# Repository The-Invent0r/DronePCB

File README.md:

# DronePCB
Drone PCB design using an Atmega328P microcontroller, MPU6050 IMU, and NRF24L01 radio module

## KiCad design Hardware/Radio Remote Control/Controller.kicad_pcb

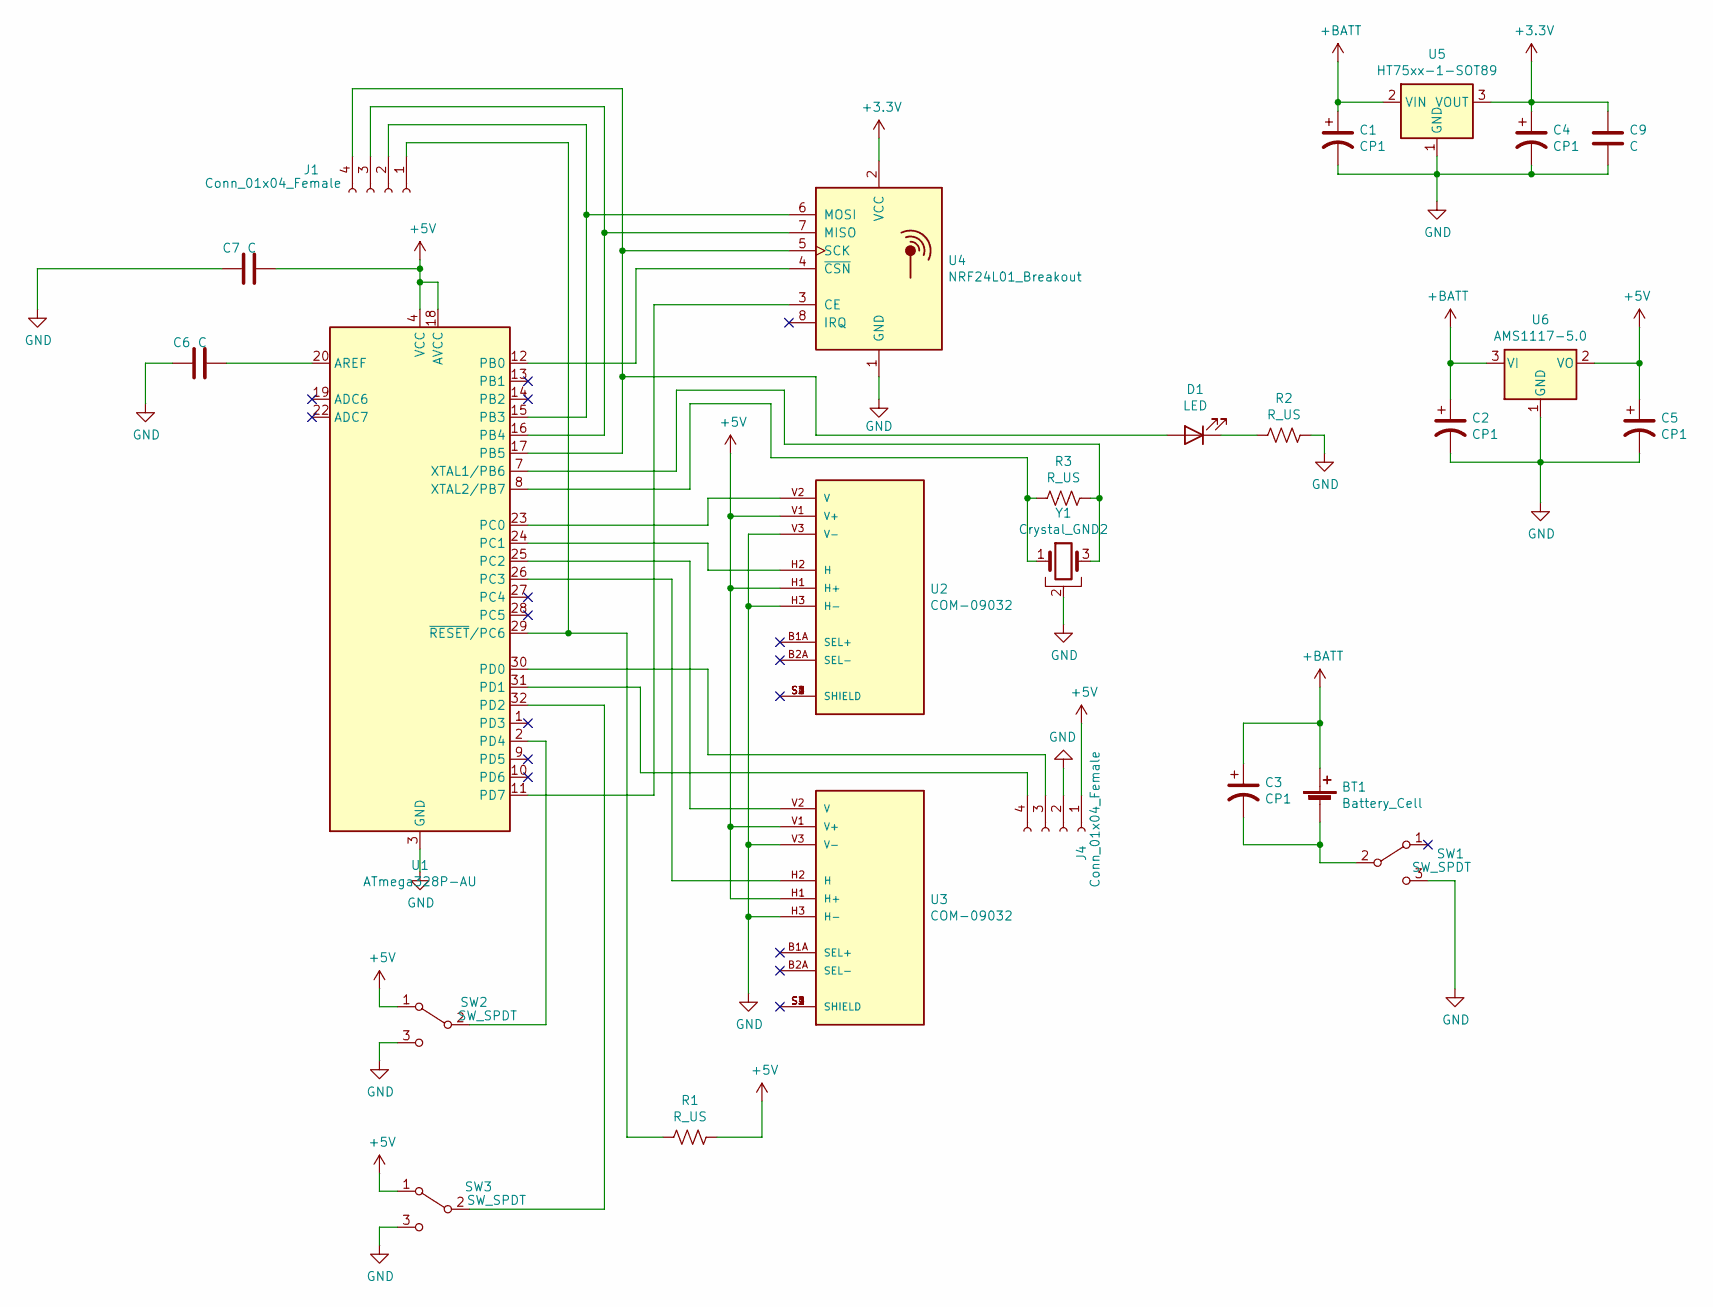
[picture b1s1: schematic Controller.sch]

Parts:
BT1: Battery_Cell; BatteryHolder_Eagle_12BH611-GR
C1, C2, C3, C4, C5: CP1; CP_EIA-3216-10_Kemet-I
C6, C7, C9: C; C_1206_3216Metric_Pad1.33x1.80mm_HandSolder
D1: LED; LED_1206_3216Metric_Pad1.42x1.75mm_HandSolder
J1, J4: Conn_01x04_Female; PinHeader_1x04_P2.54mm_Horizontal
R1, R2, R3: R_US; R_1206_3216Metric_Pad1.30x1.75mm_HandSolder
SW1, SW2, SW3: SW_SPDT; SW_Slide_1P2T_CK_OS102011MS2Q
U1: ATmega328P-AU; TQFP-32_7x7mm_P0.8mm
U2, U3: COM-09032; PARTREV N/A
U4: NRF24L01_Breakout; nRF24L01_Breakout
U5: HT75xx-1-SOT89; SOT-89-3
U6: AMS1117-5.0; SOT-223-3_TabPin2
Y1: Crystal_GND2; Resonator_SMD_muRata_CSTxExxV-3Pin_3.0x1.1mm

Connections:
+3V3: C4.1, C9.1, U4.2 (VCC), U5.3 (VOUT)
+5V: C5.1, C7.2, J4.1, R1.1, SW2.1 (A), SW3.1 (A), U1.4 (VCC), U1.6 (VCC), U1.18 (AVCC), U2.H1 (H+), U2.V1 (V+), U3.H1 (H+), U3.V1 (V+), U6.2 (VO)
+BATT: BT1.1 (+), C1.1, C2.1, C3.1, U5.2 (VIN), U6.3 (VI)
GND: C1.2, C2.2, C4.2, C5.2, C6.1, C7.1, C9.2, J4.2, R2.1, SW1.3 (C), SW2.3 (C), SW3.3 (C), U1.3 (GND), U1.5 (GND), U1.21 (GND), U2.H3 (H-), U2.V3 (V-), U3.H3 (H-), U3.V3 (V-), U4.1 (GND), U5.1 (GND), U6.1 (GND), Y1.2
unnamed: BT1.2 (-), C3.2, SW1.2 (B)
unnamed: C6.2, U1.20 (AREF)
unnamed: D1.1 (K), R2.2
unnamed: D1.2 (A), J1.4, U1.17 (PB5), U4.5 (SCK)
unnamed: J1.1, R1.2, U1.29 (~RESET~/PC6)
unnamed: J1.2, U1.15 (PB3), U4.6 (MOSI)
unnamed: J1.3, U1.16 (PB4), U4.7 (MISO)
unnamed: J4.3, U1.30 (PD0)
unnamed: J4.4, U1.31 (PD1)
unnamed: R3.1, U1.7 (XTAL1/PB6), Y1.3
unnamed: R3.2, U1.8 (XTAL2/PB7), Y1.1
unnamed: SW2.2 (B), U1.2 (PD4)
unnamed: SW3.2 (B), U1.32 (PD2)
unnamed: U1.11 (PD7), U4.3 (CE)
unnamed: U1.12 (PB0), U4.4 (~CSN)
unnamed: U1.23 (PC0), U2.V2 (V)
unnamed: U1.24 (PC1), U2.H2 (H)
unnamed: U1.25 (PC2), U3.V2 (V)
unnamed: U1.26 (PC3), U3.H2 (H)
unnamed: U2.S1 (SHIELD), U2.S2 (SHIELD), U2.S3 (SHIELD), U2.S4 (SHIELD)
unnamed: U3.S1 (SHIELD), U3.S2 (SHIELD), U3.S3 (SHIELD), U3.S4 (SHIELD)

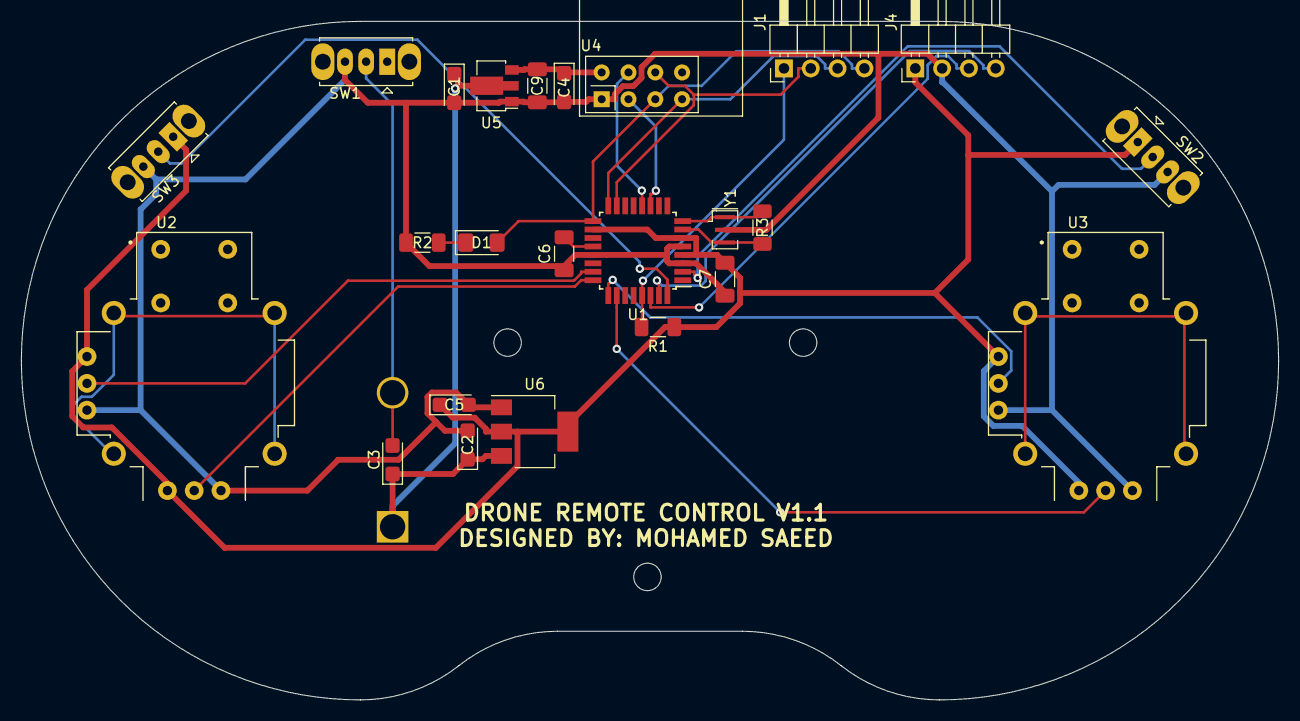
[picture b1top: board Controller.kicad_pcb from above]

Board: 2 copper layers, 119.1 x 64.3 mm, 25 parts (1 on the bottom side), 25 nets.

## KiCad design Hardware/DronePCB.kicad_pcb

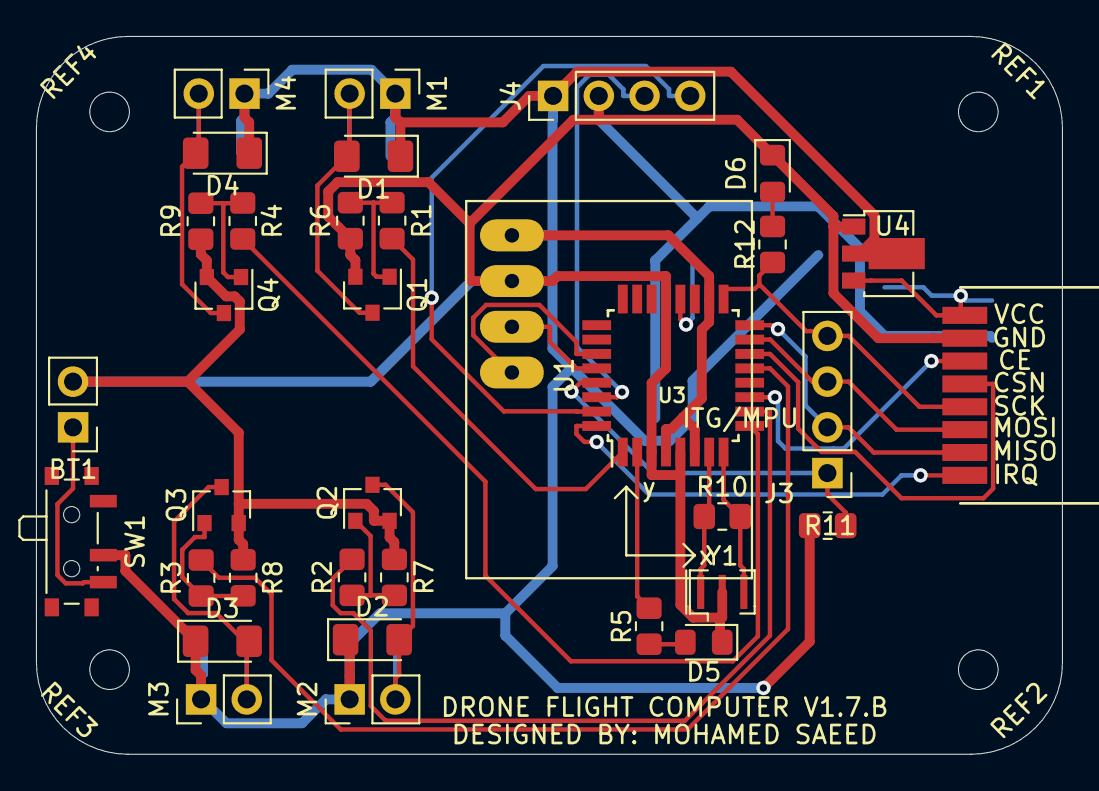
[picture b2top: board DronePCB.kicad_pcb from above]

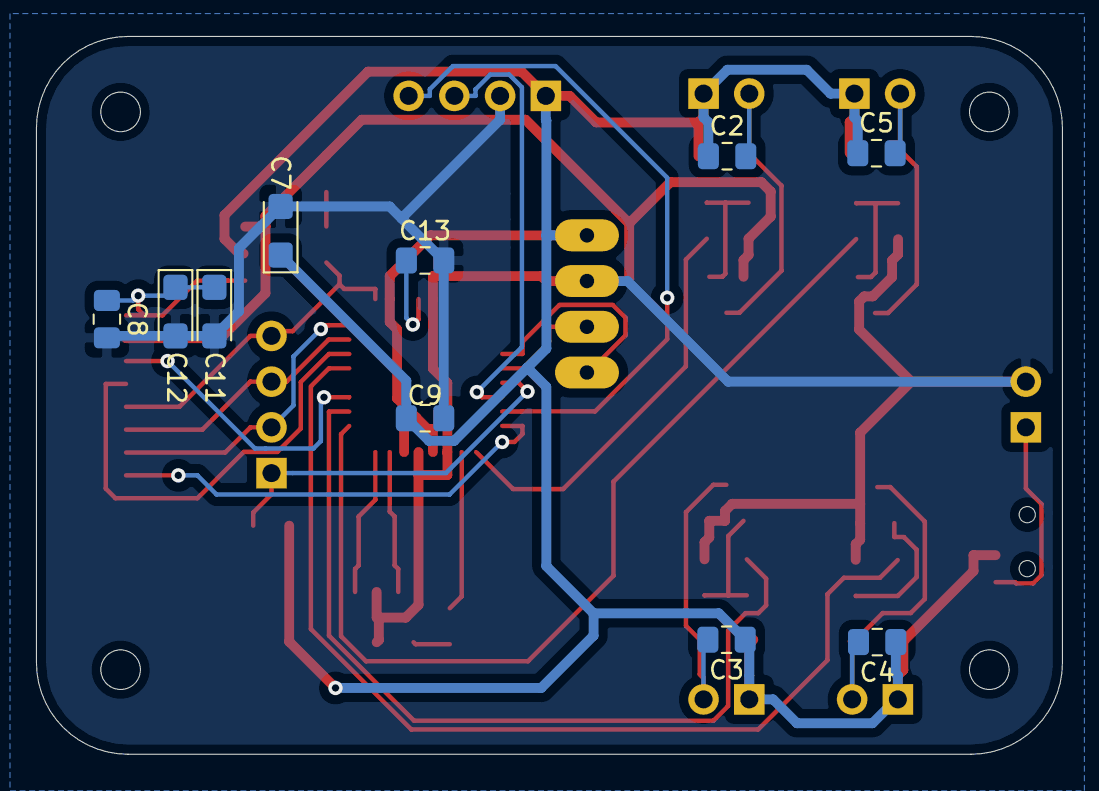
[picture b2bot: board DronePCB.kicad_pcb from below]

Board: 2 copper layers, 57.0 x 39.9 mm, 49 parts (10 on the bottom side), 33 nets.

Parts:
BT1: Battery_Cell; PinHeader_1x02_P2.54mm_Vertical
C2, C3, C4, C5, C8, C9, C13: 0.1uF; C_0805_2012Metric_Pad1.18x1.45mm_HandSolder
C7, C11, C12: 10uF; CP_EIA-3216-10_Kemet-I
D1, D2, D3, D4: D_Schottky_ALT; D_1206_3216Metric_Pad1.42x1.75mm_HandSolder
D5, D6: LED; LED_0805_2012Metric_Pad1.15x1.40mm_HandSolder
J3, J4: Conn_01x04_Female; PinHeader_1x04_P2.54mm_Vertical
M1, M2, M3, M4: Motor_DC_ALT; PinHeader_1x02_P2.54mm_Vertical
Q1, Q2, Q3, Q4: IRLML2502; SOT-23
R1, R2, R3, R4: 100R; R_0805_2012Metric_Pad1.20x1.40mm_HandSolder
R5, R12: 330R; R_0805_2012Metric_Pad1.20x1.40mm_HandSolder
R6, R7, R8, R9: 100k; R_0805_2012Metric_Pad1.20x1.40mm_HandSolder
R10: 1M; R_0805_2012Metric_Pad1.20x1.40mm_HandSolder
R11: 10k; R_0805_2012Metric_Pad1.20x1.40mm_HandSolder
REF1, REF2, REF3, REF4: MountingHole_2.2mm_M2
SW1: SW_DPDT_x2; SW_SPDT_PCM12
U1: ATmega328P-AU; TQFP-32_7x7mm_P0.8mm
U2: NRF24L01_Breakout; NRF24L01-Module-SMD
U3: GY-521
U4: HT75xx-1-SOT89; SOT-89-3
Y1: Crystal_GND2; Resonator_SMD_muRata_CSTxExxV-3Pin_3.0x1.1mm

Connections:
+3V3: C8.1, C11.1, C12.1, U2.1, U4.3
+BATT: C2.1, C3.1, C4.1, C5.1, C7.1, C9.2, D1.1, D2.1, D3.1, D4.1, J4.1, M1.1, M2.1, M3.1, M4.1, R11.1, SW1.2, U1.4, U1.6, U1.18, U3.VCC, U4.2
BackLeft: R4.2, U1.9
BackRight: R3.2, U1.13
CE: U1.11, U2.3
FrontLeft: R1.2, U1.1
FrontRight: R2.2, U1.10
GND: BT1.2, C7.2, C8.2, C9.1, C11.2, C12.2, C13.2, D5.1, D6.1, J4.2, Q1.2, Q2.2, Q3.2, Q4.2, R6.1, R7.1, R8.1, R9.1, U1.3, U1.5, U1.21, U2.2, U3.GND, U4.1, Y1.2
IRQ: U1.32, U2.8
MISO: J3.2, U1.16, U2.7
MOSI: J3.3, U1.15, U2.6
unnamed: BT1.1, SW1.3
unnamed: C2.2, D1.2, M1.2, Q1.3
unnamed: C3.2, D2.2, M2.2, Q2.3
unnamed: C4.2, D3.2, M3.2, Q3.3
unnamed: C5.2, D4.2, M4.2, Q4.3
unnamed: C13.1, U1.20
unnamed: D5.2, R5.1
unnamed: D6.2, R12.1
unnamed: Q1.1, R1.1, R6.2
unnamed: Q2.1, R2.1, R7.2
unnamed: Q3.1, R3.1, R8.2
unnamed: Q4.1, R4.1, R9.2
unnamed: R5.2, U1.2
unnamed: R10.1, U1.7, Y1.1
unnamed: R10.2, U1.8, Y1.3
RX: J4.3, U1.30
Reset: J3.1, R11.2, U1.29
SCK: J3.4, R12.2, U1.17, U2.5
SCL: U1.28, U3.SCL
SDA: U1.27, U3.SDA
TX: J4.4, U1.31
~CSN: U1.14, U2.4

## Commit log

2024-04-04 Create Hardware
    Kicad schematic and associated hardware.
2024-04-04 Create hardware
    Kicad Schematics and associated hardware
2024-04-04 Create software
    Multiwii software for running drone. Based off of Electronoobs brushed dc motor drone code.
2024-04-04 Create flight controller
    Software for flight controller board.
2024-04-04 Create radio remote controller
    Software for radio remote controller
2024-04-04 Create radio remote control
    Radio Remote Control
